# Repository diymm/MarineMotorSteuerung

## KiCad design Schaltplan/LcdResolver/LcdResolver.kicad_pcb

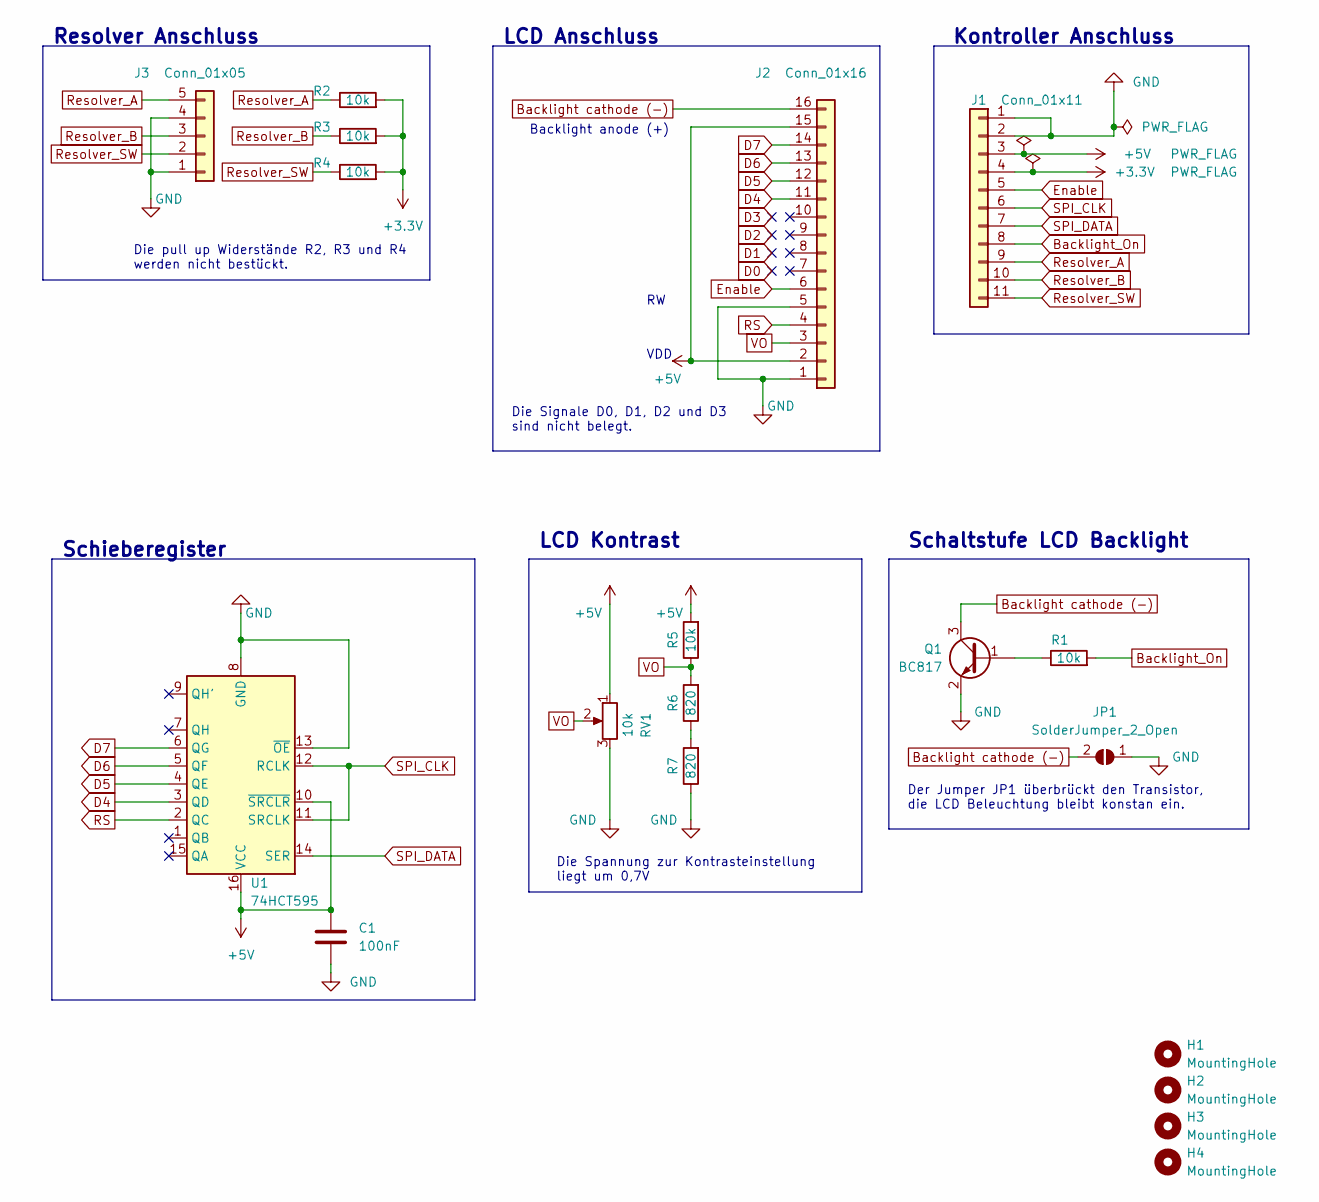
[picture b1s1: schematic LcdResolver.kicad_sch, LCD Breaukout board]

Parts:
C1: 100nF; C_0805_2012Metric
H1, H2, H3, H4: MountingHole; MountingHole_3.2mm_M3
J1: Conn_01x11; PinHeader_1x11_P2.54mm_Vertical
J2: Conn_01x16; PinHeader_1x16_P2.54mm_Vertical
J3: Conn_01x05; PinHeader_1x05_P2.54mm_Vertical
JP1: SolderJumper_2_Open; SolderJumper-2_P1.3mm_Open_RoundedPad1.0x1.5mm
Q1: BC817; SOT-23
R1, R2, R3, R4, R5: 10k; R_0805_2012Metric
R6, R7: 820; R_0805_2012Metric
RV1: 10k; Potentiometer_Piher_PT-6-V_Vertical
U1: 74HCT595; SOP-16_4.55x10.3mm_P1.27mm

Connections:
+3.3V: J1.4, R2.2, R3.2, R4.2
+5V: C1.1, J1.3, J2.2, J2.15, R5.2, RV1.1, U1.10 (~SRCLR), U1.16 (VCC)
Backlight cathode (-): J2.16, JP1.2 (B), Q1.3 (C)
Backlight_On: J1.8, R1.2
D4: J2.11, U1.3 (QD)
D5: J2.12, U1.4 (QE)
D6: J2.13, U1.5 (QF)
D7: J2.14, U1.6 (QG)
Enable: J1.5, J2.6
GND: C1.2, J1.1, J1.2, J2.1, J2.5, J3.1, J3.4, JP1.1 (A), Q1.2 (E), R7.1, RV1.3, U1.8 (GND), U1.13 (~OE)
unnamed: Q1.1 (B), R1.1
unnamed: R6.1, R7.2
RS: J2.4, U1.2 (QC)
Resolver_A: J1.9, J3.5, R2.1
Resolver_B: J1.10, J3.3, R3.1
Resolver_SW: J1.11, J3.2, R4.1
SPI_CLK: J1.6, U1.11 (SRCLK), U1.12 (RCLK)
SPI_DATA: J1.7, U1.14 (SER)
VO: J2.3, R5.1, R6.2, RV1.2

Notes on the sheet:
Schaltstufe LCD Backlight
LCD Kontrast
LCD Anschluss
Schieberegister
Die Signale D0, D1, D2 und D3 sind nicht belegt.
Der Jumper JP1 überbrückt den Transistor, die LCD Beleuchtung bleibt konstan ein.
Resolver Anschluss
Die pull up Widerstände R2, R3 und R4 werden nicht bestückt.
Kontroller Anschluss
Die Spannung zur Kontrasteinstellung liegt um 0,7V
VDD
Backlight anode (+)

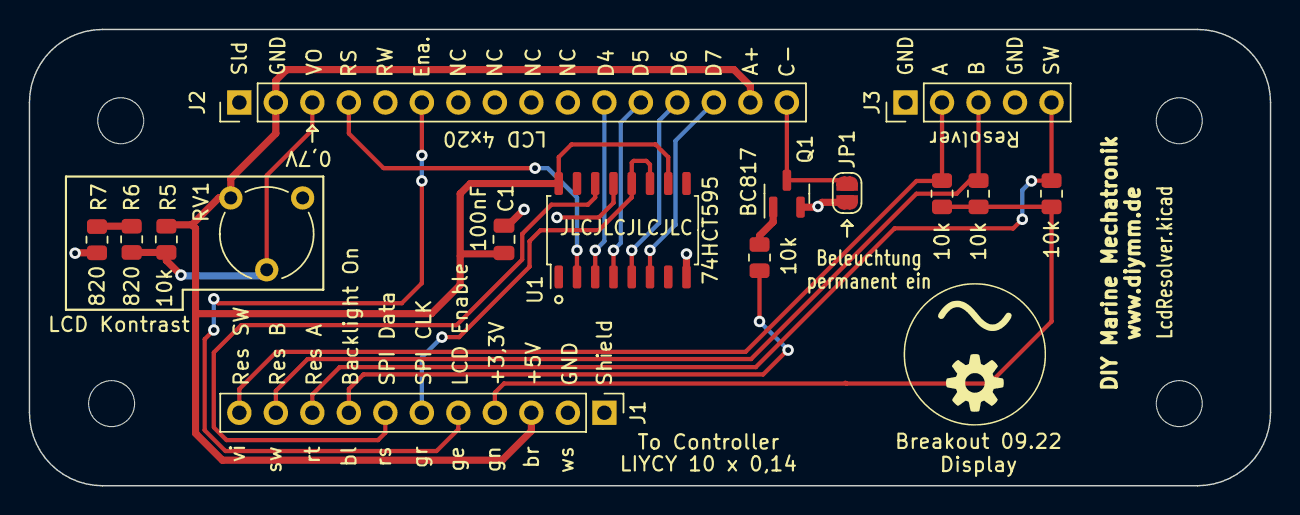
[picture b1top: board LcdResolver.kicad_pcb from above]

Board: 2 copper layers, 86.4 x 31.8 mm, 19 parts (0 on the bottom side), 19 nets.

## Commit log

2022-09-13 Start
    Erster commit
2022-10-24 Schaltplan für das LCD Resolver/Board
    Schaltplan für das LCD/Resolver hinzugefügt, inklusive Gerber Dateien.
2022-10-30 Fehlerhafte Resolverplatine gelöscht
    Die Resolverplatine hhatte schwerwiegende Fehler
